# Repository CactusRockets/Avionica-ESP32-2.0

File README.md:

# Placas da aviônica para o foguete de teste

Nesse repositório temos os arquivos das placas que farão parte da aviônica do foguete de teste da Cactus Rockets Design.

### Descrição

Temos duas placas principais para esta aviônica:
- Placa de Processamento
- Placa de Acionamento

A placa de processamento é responsável pelo processamento dos dados dos módulos, armazenamento desses dados e telemetria. A placa de acionamento possui o circuito necessário para a correta ativação do Skib.

OBS.: Os arquivos das placas podems ser abertos por meio software Eagle da Autodesk.

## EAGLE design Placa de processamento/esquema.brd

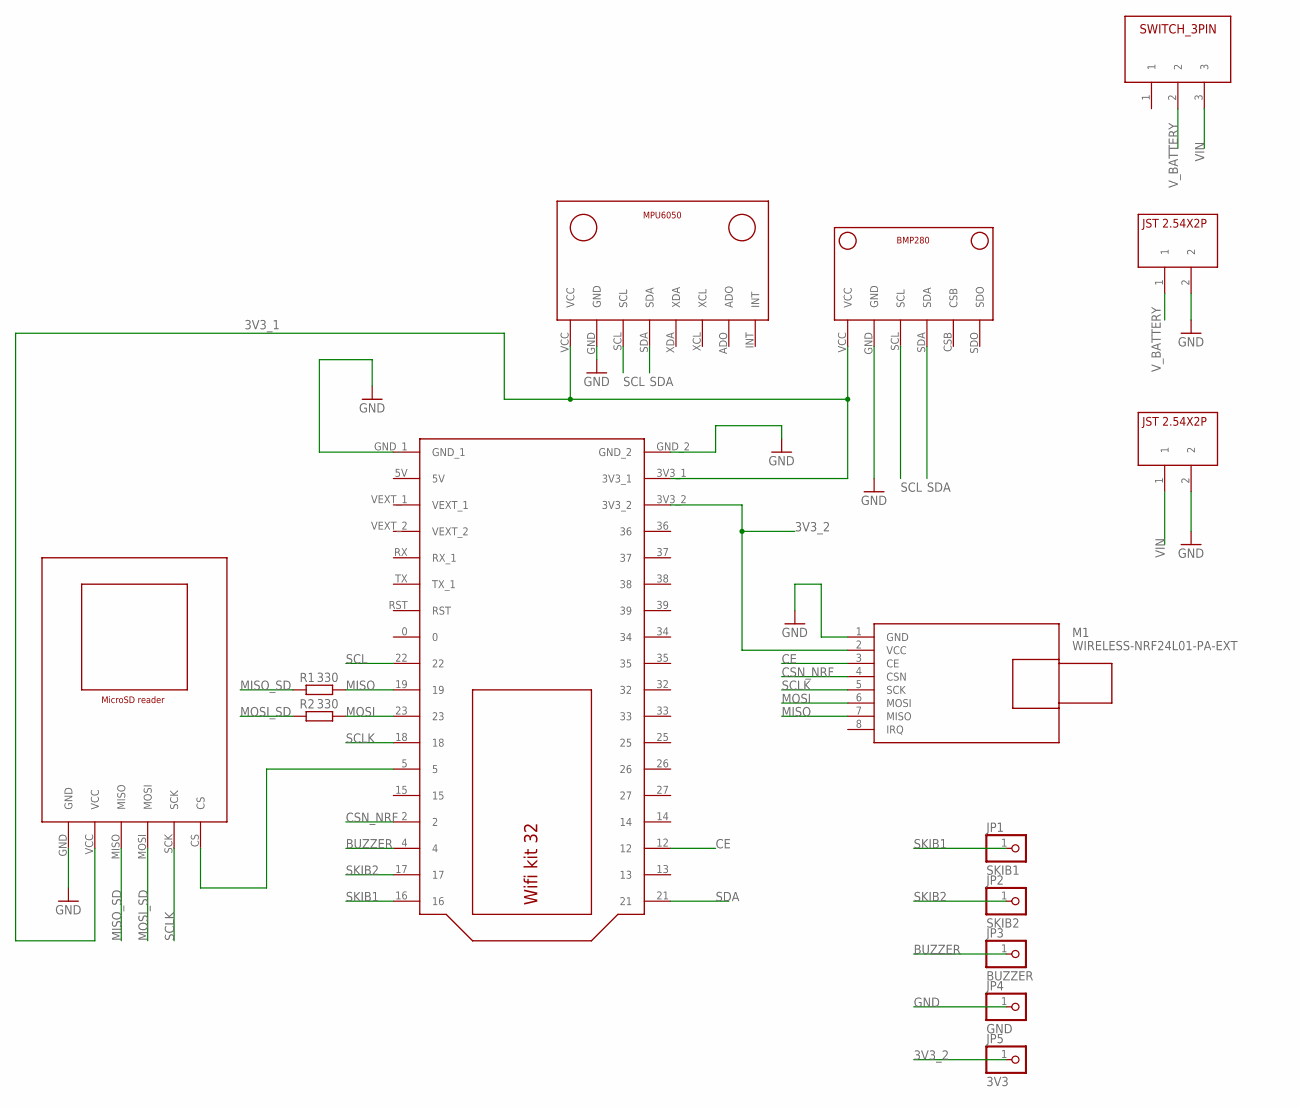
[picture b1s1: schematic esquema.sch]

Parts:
JP1: SKIB1; 1X01
JP2: SKIB2; 1X01
JP3: BUZZER; 1X01
JP4: GND; 1X01
JP5: 3V3; 1X01
M1: WIRELESS-NRF24L01-PA-EXT
R1, R2: 330; 0207/10
U$1: BMP280V1; BMP280_FOOTPRINT
U$2: MICROSD_READER; MICROSD_READER_FOOTPRINT
U$3: MPU6050V1; MPU6050_FOOTPRINT
U$4: WIFI_KIT32
U$5, U$7: JST2.54X2P; JST2.54X2P_FOOTPRINT
U$6: SWITCH_3PIN

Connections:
3V3_1: U$1.VCC, U$2.VCC, U$3.VCC, U$4.3V3_1
3V3_2: JP5.1, M1.2 (VCC), U$4.3V3_2
BUZZER: JP3.1, U$4.4
CE: M1.3 (CE), U$4.12
CSN_NRF: M1.4 (CSN), U$4.2
GND: JP4.1, M1.1 (GND), U$1.GND, U$2.GND, U$3.GND, U$4.GND_1, U$4.GND_2, U$5.2, U$7.2
MISO: M1.7 (MISO), R1.2, U$4.19
MISO_SD: R1.1, U$2.MISO
MOSI: M1.6 (MOSI), R2.2, U$4.23
MOSI_SD: R2.1, U$2.MOSI
unnamed: U$2.CS, U$4.5
SCL: U$1.SCL, U$3.SCL, U$4.22
SCLK: M1.5 (SCK), U$2.SCK, U$4.18
SDA: U$1.SDA, U$3.SDA, U$4.21
SKIB1: JP1.1, U$4.16
SKIB2: JP2.1, U$4.17
VIN: U$6.3, U$7.1
V_BATTERY: U$5.1, U$6.2

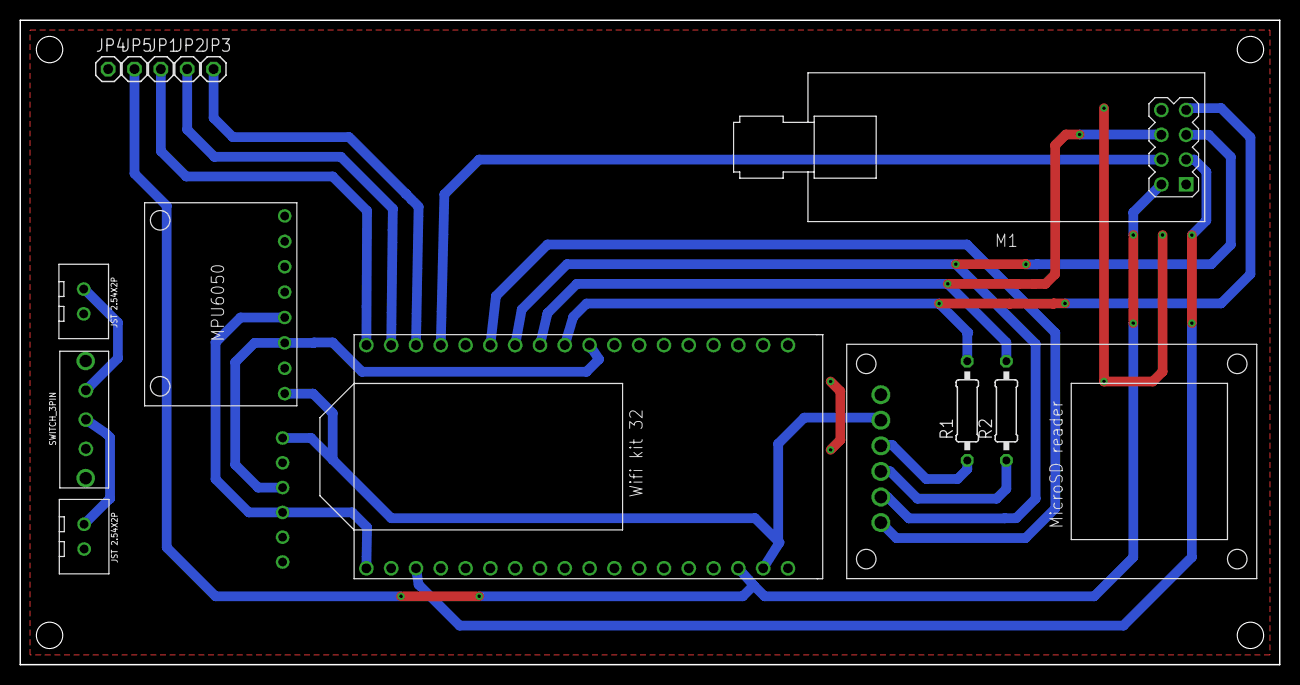
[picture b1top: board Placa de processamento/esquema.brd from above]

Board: 2 copper layers, 129.0 x 66.0 mm, 15 parts (1 on the bottom side), 18 nets.

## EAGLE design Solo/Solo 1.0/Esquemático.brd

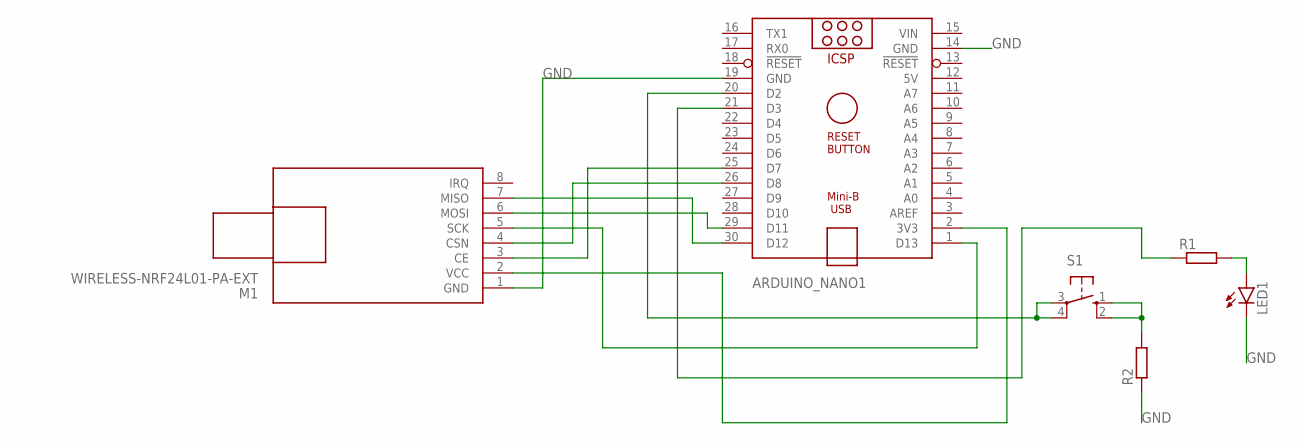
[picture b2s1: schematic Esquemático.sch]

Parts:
ARDUINO_NANO1: ARDUINO_NANO
LED1: LED5MM
M1: WIRELESS-NRF24L01-PA-EXT
R1, R2: R-EU_0207/10; 0207/10
S1: 10-XX; B3F-10XX

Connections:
5V: ARDUINO_NANO1.12 (5V)
GND: ARDUINO_NANO1.14 (GND), ARDUINO_NANO1.19 (GND), LED1.K (C), M1.1 (GND), R2.1
unnamed: LED1.A, R1.2
unnamed: ARDUINO_NANO1.20 (D2), S1.3, S1.4 (P1)
unnamed: R2.2, S1.1 (S), S1.2 (S1)
unnamed: ARDUINO_NANO1.21 (D3), R1.1
unnamed: ARDUINO_NANO1.1 (D13), M1.5 (SCK)
unnamed: ARDUINO_NANO1.30 (D12), M1.7 (MISO)
unnamed: ARDUINO_NANO1.29 (D11), M1.6 (MOSI)
unnamed: ARDUINO_NANO1.25 (D7), M1.3 (CE)
unnamed: ARDUINO_NANO1.26 (D8), M1.4 (CSN)
unnamed: ARDUINO_NANO1.2 (3V3), M1.2 (VCC)
VIN: ARDUINO_NANO1.15 (VIN)

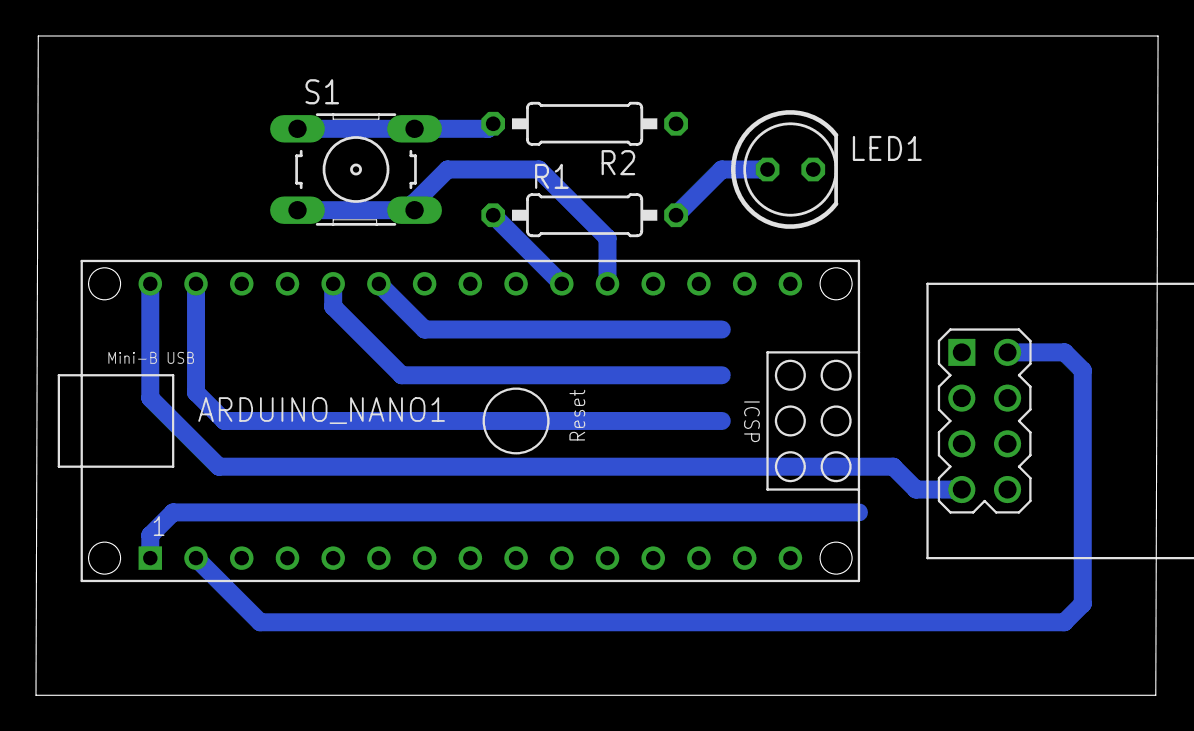
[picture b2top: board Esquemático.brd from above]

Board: 2 copper layers, 62.3 x 36.6 mm, 6 parts (0 on the bottom side), 11 nets.

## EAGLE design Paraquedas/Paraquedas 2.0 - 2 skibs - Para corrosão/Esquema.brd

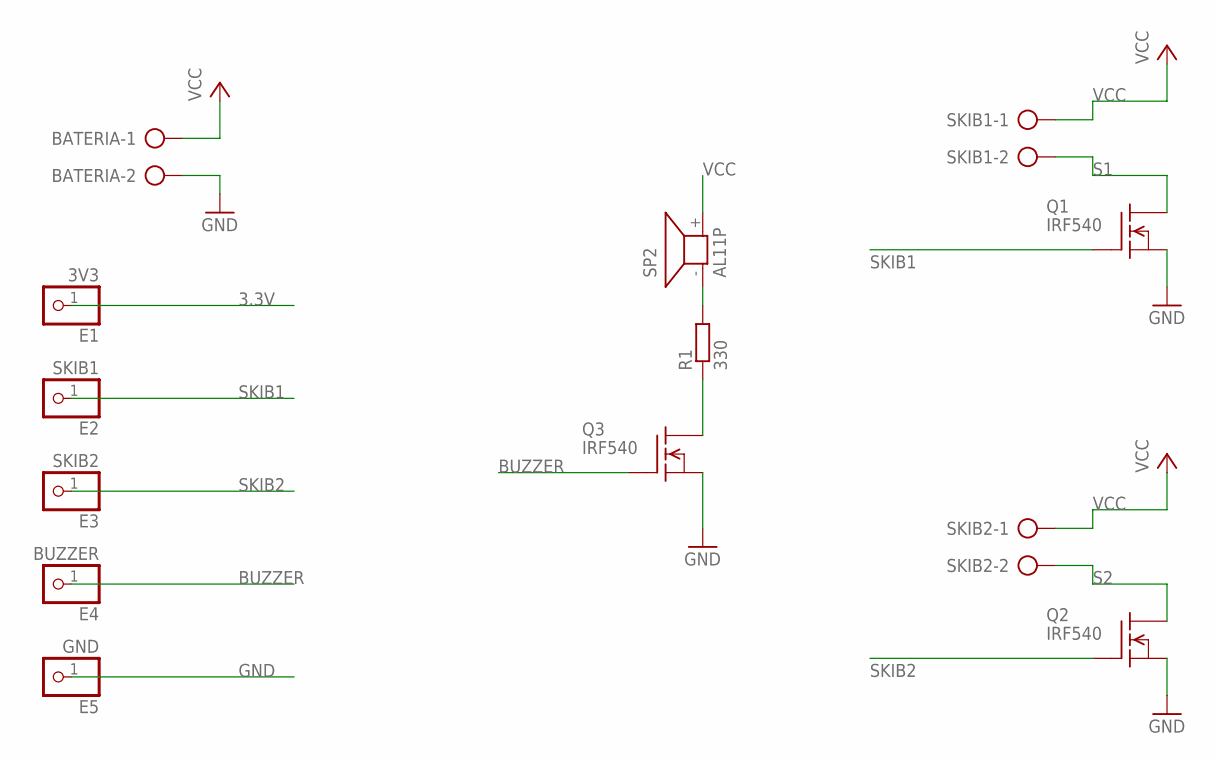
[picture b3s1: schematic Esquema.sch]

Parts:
BATERIA: AK500/2-H
E1: 3V3; 1X01
E2: SKIB1; 1X01
E3: SKIB2; 1X01
E4: BUZZER; 1X01
E5: GND; 1X01
Q1, Q2, Q3: IRF540; TO220
R1: 330; 0207/10
SKIB1, SKIB2: AK500/2-H
SP2: AL11P

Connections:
3.3V: E1.1
BUZZER: E4.1, Q3.1 (G)
GND: BATERIA.2, E5.1, Q1.3 (S), Q2.3 (S), Q3.3 (S)
unnamed: Q3.2 (D), R1.1
unnamed: R1.2, SP2.- (1)
S1: Q1.2 (D), SKIB1.2
S2: Q2.2 (D), SKIB2.2
SKIB1: E2.1, Q1.1 (G)
SKIB2: E3.1, Q2.1 (G)
VCC: BATERIA.1, SKIB1.1, SKIB2.1, SP2.+ (2)

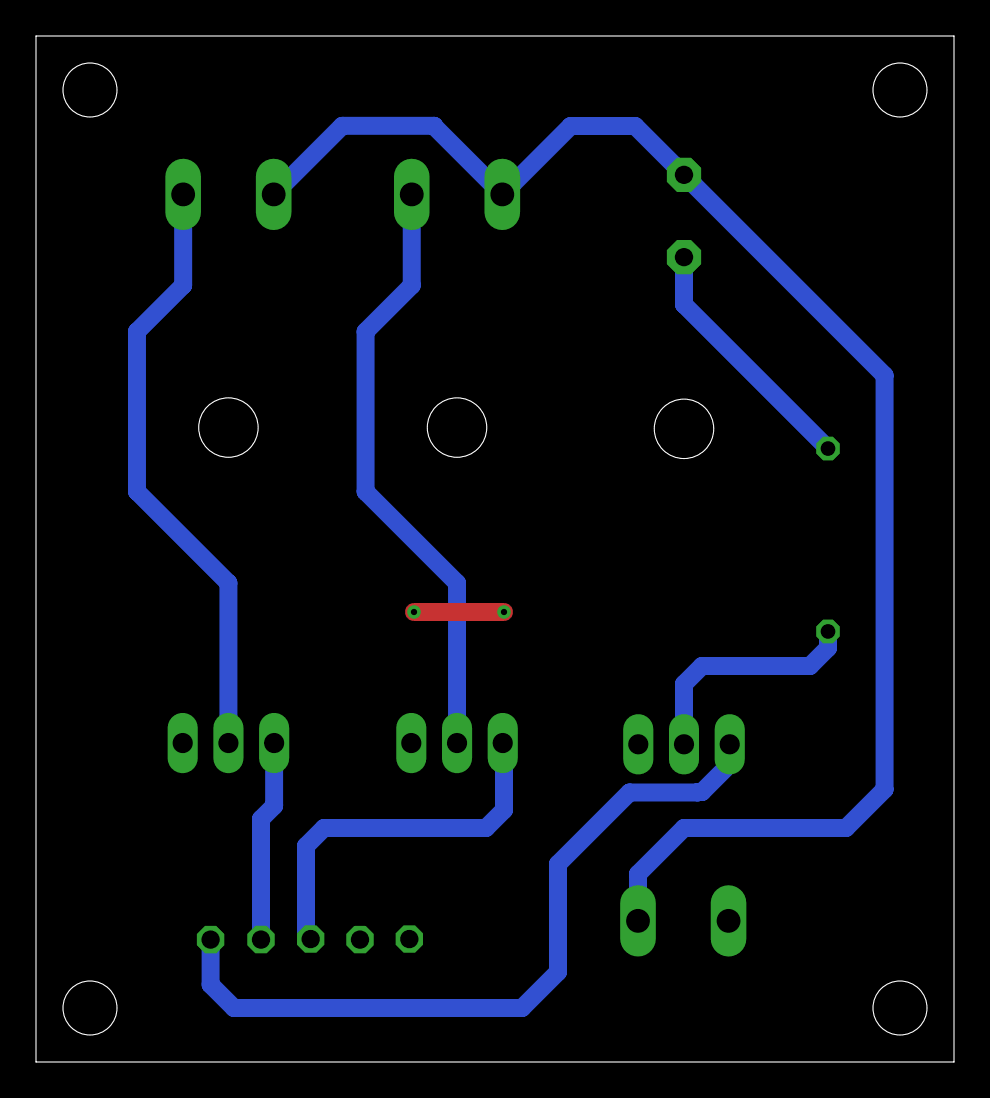
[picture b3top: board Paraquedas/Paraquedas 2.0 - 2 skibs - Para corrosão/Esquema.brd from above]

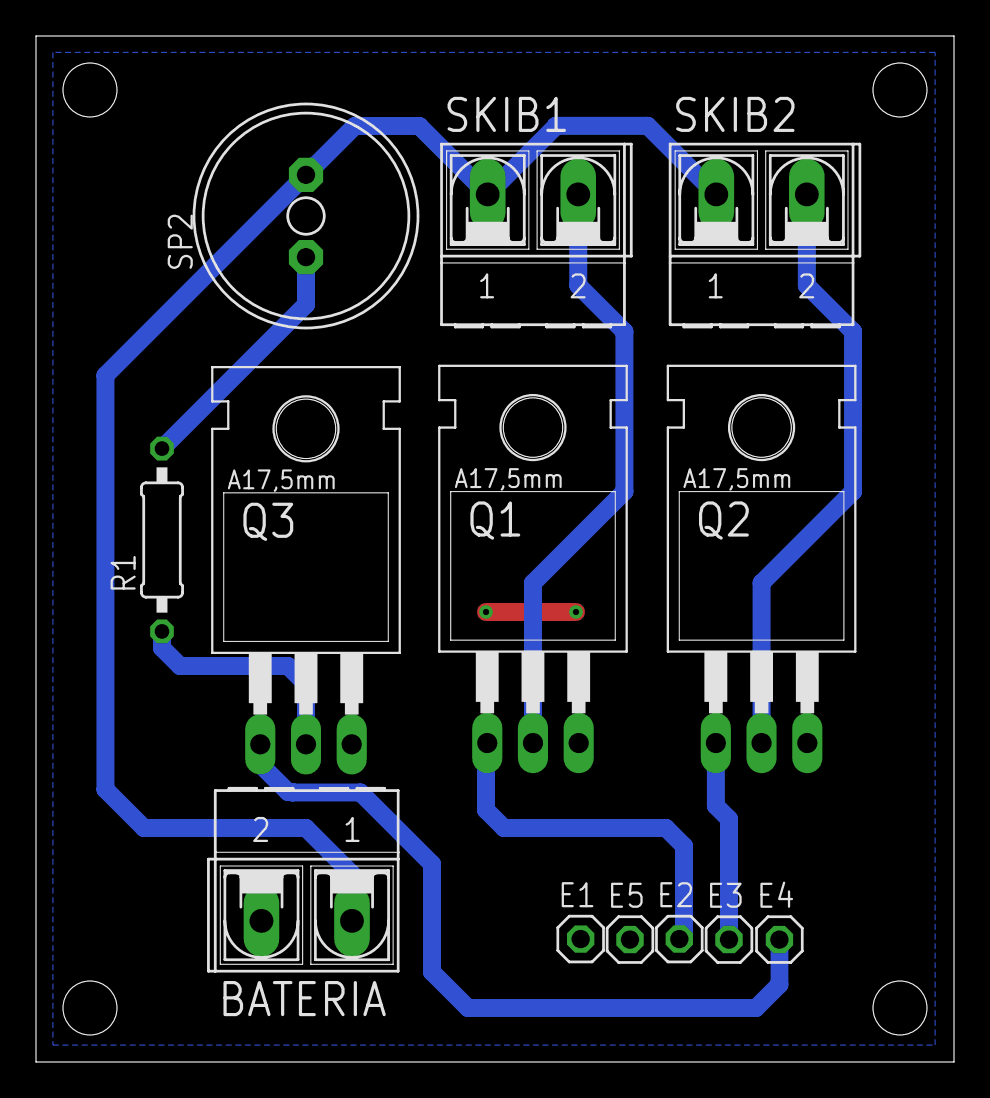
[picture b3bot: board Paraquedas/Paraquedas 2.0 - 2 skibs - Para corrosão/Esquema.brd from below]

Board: 2 copper layers, 51.0 x 57.0 mm, 13 parts (13 on the bottom side), 9 nets.

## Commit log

2023-05-04 Atualizando placas
2023-07-30 Message
2023-11-14 Upgrage

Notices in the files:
parts and their libraries:
modules: Released under the Creative Commons Attribution 4.0 International License: http://creativecommons.org/licenses/by/4.0
